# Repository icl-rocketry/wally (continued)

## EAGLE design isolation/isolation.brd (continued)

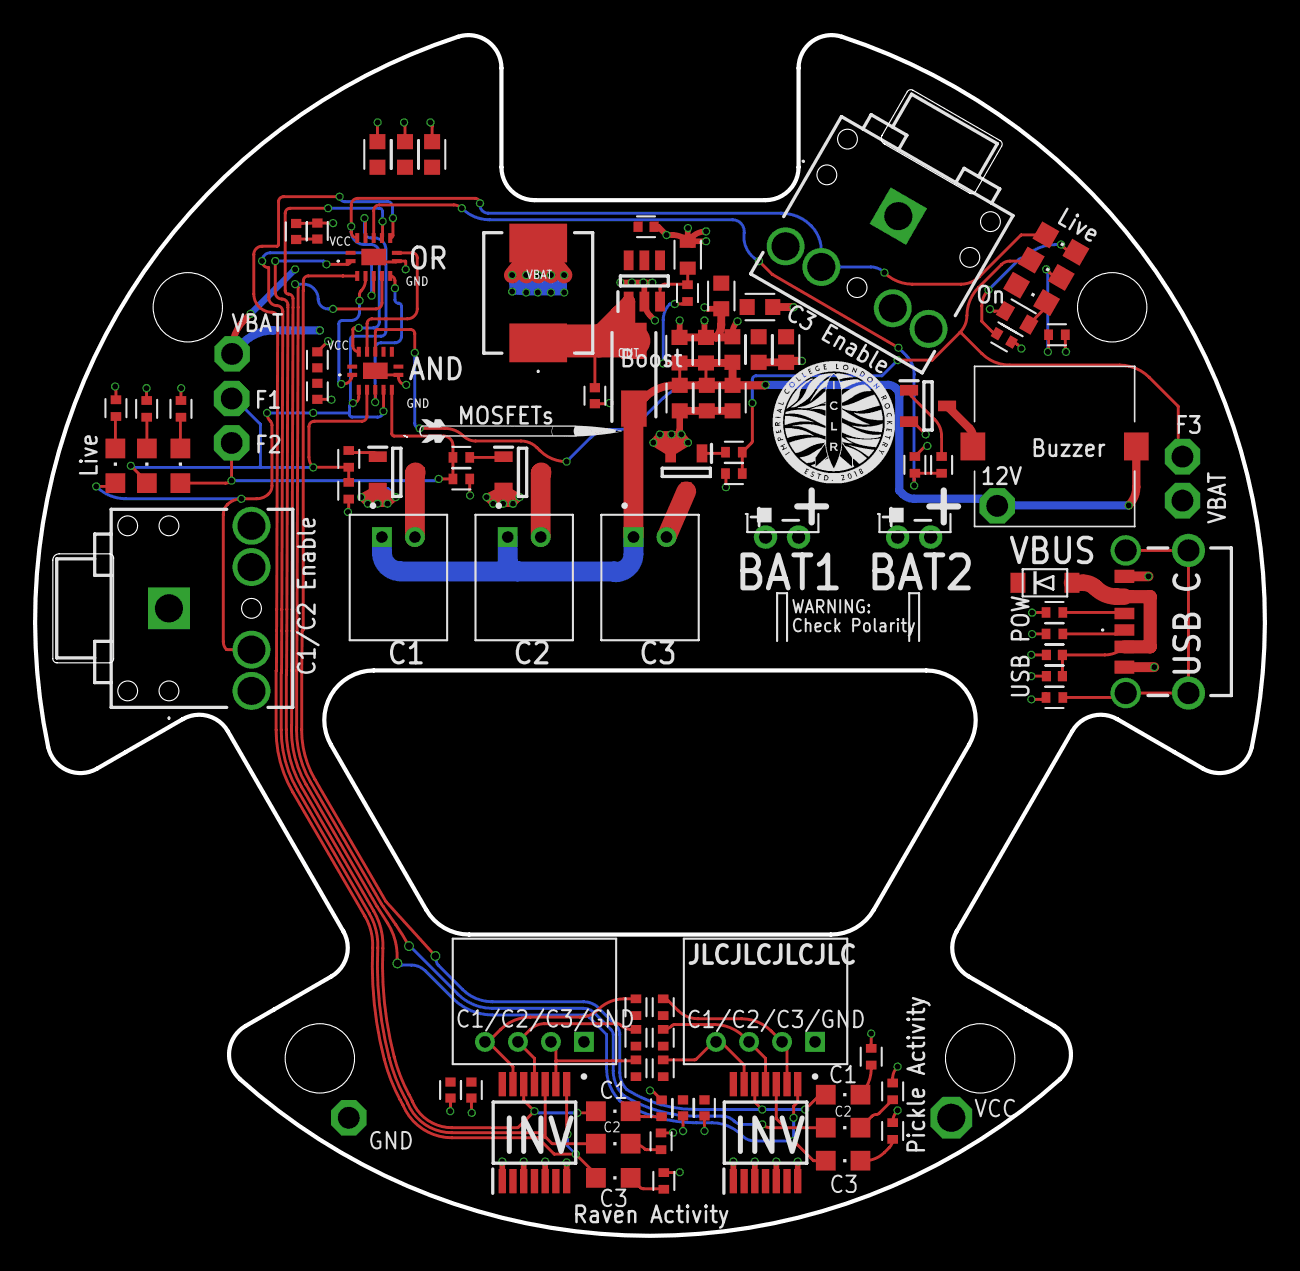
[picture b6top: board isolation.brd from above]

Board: 2 copper layers, 74.5 x 72.7 mm, 99 parts (0 on the bottom side), 50 nets.

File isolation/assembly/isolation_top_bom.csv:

Comment,Designator,Footprint,LCSC Part #
1M,R2 R13,RESC1608X60,C22935
1u,C3 C9 C11 C13 C15,CAPC1608X85,C15849
5k1,R12 R14,RESC1608X60,C23186
10u,C1 C2 C16 C17 C18 C19,CAPC1608X85,C19702
10uH,L1,L0603,C1035
22u,C4 C5 C6 C7 C20 C21 C22,CAPC1608X85,C59461
68k,R3 R8 R9 R10 R11,RESC1608X60,C23231
75,R1,RESC1608X60,C4275
100,R6 R7,RESC1608X60,C22775
100n,C8 C10 C12 C14,CAPC1608X85,C14663
120,R4 R5 R15 R16 R17 R18 R19 R20 R21 R22 R23,RESC1608X60,C22787
470,R24 R25 R26 R27,RESC1608X60,C23179
10164359-00011LF,J7,1016435900011LF,
CMI-9705-85-SMT-TR,LS1,CMI970585SMTTR,
FDN359BN,IC5 IC6 IC7 IC8,SOT95P251X112-3N,C5290365
LEDG,LED3 LED5,CHIPLED_0805,C2297
LEDR,LED6 LED7 LED8 LED9 LED10 LED11 LED12 LED13 LED14,CHIPLED_0805,C84256
LEDW,LED1,CHIPLED_0805,C34499
LEDY,LED2 LED4,CHIPLED_0805,C2296
SN74HC14PWR,IC2,SOP65P640X120-14N,SN74HC14PWR
SN74HCS08DYYR,IC4,SOP50P326X110-14N,
SN74HCS32BQAR,IC3,SN74HCS32BQAR,
SSA34-E3_5AT,D1,DIOM5127X229N,C22452
USBDiode,D2,SOD-123FL,C64898
XTLV61048DBVR,IC1,SOT95P280X145-6N,C2861467

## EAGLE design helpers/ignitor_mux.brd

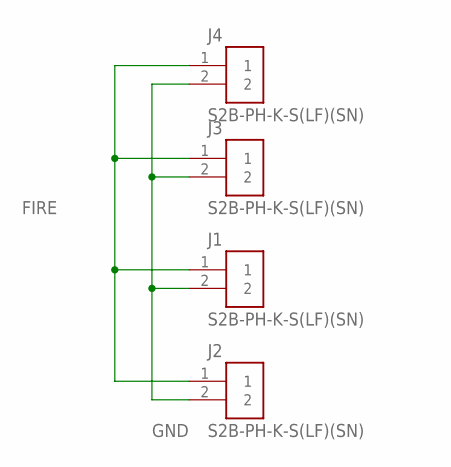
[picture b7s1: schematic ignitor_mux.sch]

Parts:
J1, J2, J3, J4: S2B-PH-K-S(LF)(SN)

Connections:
FIRE: J1.1, J2.1, J3.1, J4.1
GND: J1.2, J2.2, J3.2, J4.2

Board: 2 copper layers, 4 parts (0 on the bottom side), 2 nets, no tracks yet.

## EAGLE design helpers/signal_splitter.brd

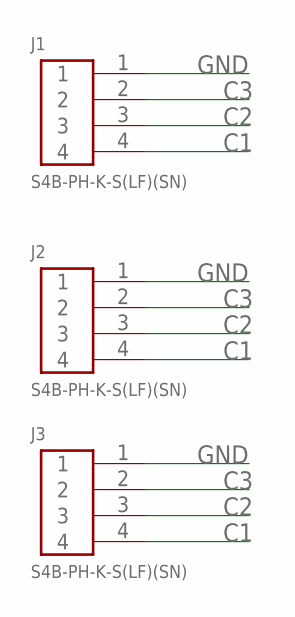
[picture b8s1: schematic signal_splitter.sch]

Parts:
J1, J2, J3: S4B-PH-K-S(LF)(SN)

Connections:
C1: J1.4, J2.4, J3.4
C2: J1.3, J2.3, J3.3
C3: J1.2, J2.2, J3.2
GND: J1.1, J2.1, J3.1

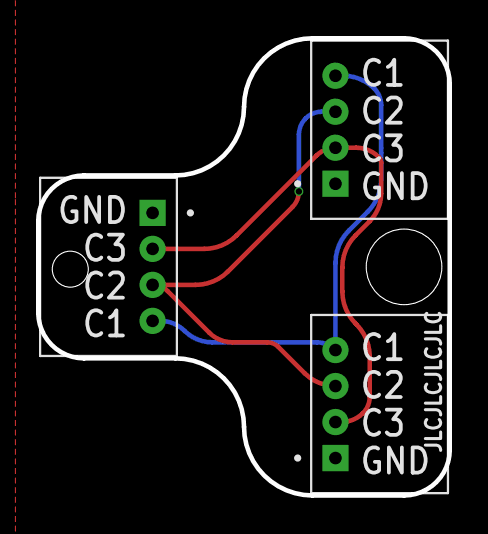
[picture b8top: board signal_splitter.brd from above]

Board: 2 copper layers, 22.9 x 25.4 mm, 3 parts (0 on the bottom side), 4 nets.

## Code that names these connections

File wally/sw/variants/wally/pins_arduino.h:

#ifndef Pins_Arduino_h
#define Pins_Arduino_h

#include <stdint.h>
#include "soc/soc_caps.h"

#define USB_VID            0x239A
#define USB_PID            0x8145
#define USB_MANUFACTURER   "ICLR"
#define USB_PRODUCT        "WALLY"
#define USB_SERIAL         ""   // Empty string for MAC adddress

#define PIN_BUTTON1     0  // BOOT0 switch

// UART
static const uint8_t TX0 = 43;
static const uint8_t RX0 = 44;

static const uint8_t TX1 = 17;
static const uint8_t RX1 = 18;

// I2C
static const uint8_t SDA0 = 47;
static const uint8_t SCL0 = 21;

static const uint8_t SDA1 = 5;
static const uint8_t SCL1 = 4;

// SD
static const uint8_t SD_CS   = 14;
static const uint8_t SD_DO   = 42;
static const uint8_t SD_CLK  = 39;
static const uint8_t SD_DI   = 21;

// Radio
static const uint8_t RAD_CS   = 39;
static const uint8_t RAD_DO   = 37;
static const uint8_t RAD_CLK  = 36;
static const uint8_t RAD_DI   = 38;
static const uint8_t RAD_RST  = 40;
static const uint8_t RAD_DIO1 = 42;
static const uint8_t RAD_DIO2 = 2;
static const uint8_t RAD_DIO3 = 1;
static const uint8_t RAD_RXEN  = 35;
static const uint8_t RAD_TXEN  = 41;
static const uint8_t RAD_BUSY = 48;

// SPI defaults (for compatibility with SPI lib)
static const uint8_t SCK  = RAD_CLK;
static const uint8_t MISO = RAD_DO;
static const uint8_t MOSI = RAD_DI;
static const uint8_t SS   = RAD_CS;

// I2C defaults (for compatibility with Wire lib)
static const uint8_t SDA = SDA0;
static const uint8_t SCL = SCL0;

// GPIO
static const uint8_t A0 = 8;
static const uint8_t A1 = 10;
static const uint8_t A2 = 9;
static const uint8_t A3 = 6;
static const uint8_t A4 = 16;

#define LED_R    8
#define LED_Y   10
#define LED_G    9

// VSENSE
static const uint8_t VSENSE = 7;

// PPS
static const uint8_t PPS = 15;

#endif /* Pins_Arduino_h */

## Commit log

2023-01-31 Wally
2023-01-31 Learning to use eagle
2023-02-07 wally board with gps and lora
2023-03-04 did code stuff
2023-03-07 sorry bout this
2023-03-07 tried to continue code
2023-03-21 complete code
2023-04-28 Added lora code (Doesn't work)
2023-05-20 Tiny GPS Uploaded
    Have installed tiny GPS module to Wally. (As advised by Shrey) :D
2023-05-20 Tiny GPS added
    I have added tiny gps as advised by Shrey to our lora branch. After having to use terminal wizzardry to add it (pain) :(
2023-05-20 Added Tiny GPS module
    As advised by Shrey
2023-05-23 LoRa Library Added
    Added the LoRa library as advised by Akshat.
2023-05-23 Create SX126x-Arduino
    LoRa library added as advised by Akshat:
    https://github.com/beegee-tokyo/SX126x-Arduino
2023-12-12 github testing 1.
    just testing on push/pulling
2023-12-12 deleted fixed
2023-12-12 creation of the file
2023-12-12 initial code
2023-12-12 Points in a plot for test rocket
2024-01-23 Update test data generation
    Creates time received values array for all ground stations for our full parabola fake rocket flight
2024-01-27 Update testdatagen.py
    Began working on the code to reconstruct the trajectory from the time recorded.
2024-01-30 some disaster
2024-02-03 03 Feb 2024
    Calculated point on intersection + coordinates of the point. Need to find normal vector to continue.
2024-02-06 final problem
2024-02-10 tests
2024-02-10 z diff fix
2024-02-20 Add files via upload
    Initial PCB design for ground station
2024-02-24 sustainer wiring diagram
2024-02-24 Added SIRIUS_sustainer.drawio
2024-02-24 power arch
2024-02-24 main boards
2024-02-24 complete IO
2024-02-24 wiring
2024-02-24 add qd
2024-02-24 antennae
2024-02-24 thermocouple
2024-03-19 Add files via upload
    Version 1 of Ground Station PCB
2024-04-25 create blank schematics for isolation board
2024-04-25 battery connectors
2024-04-25 power indicator LED
2024-04-26 12v boost schematic complete
2024-04-26 headphone jacks for user input
2024-04-26 fix footprint for caps
2024-04-26 headphone jack with inverter
2024-04-26 jst inputs from flight computers
2024-04-26 invert raven inputs
2024-04-26 complete firing logic
2024-04-26 fire control mosfet
2024-04-26 pull down resistors on mosfets
2024-04-26 danger buzzer
2024-04-26 usb c power
2024-04-26 indicator LEDs with manual testing
2024-04-26 ust jst for power
2024-04-26 layout with stringers and xc
2024-04-26 2 sector approach
2024-04-26 switch to JST-PH
2024-04-27 physically placed
2024-04-27 manual routing complete
2024-04-27 set board outline from dxf
2024-04-27 pads for ext power in
2024-04-27 ground and vcc pours
2024-04-27 wire lower connectors
2024-04-27 more routing
2024-04-27 10mil dim line
2024-04-27 move to smaller inverter
2024-04-27 smaller OR IC
2024-04-27 2 pin ignitor connectors
2024-04-27 add test pads
2024-04-27 placed shrunken components
2024-04-27 central cutout
2024-04-27 final routing
2024-04-27 fix to drc
2024-04-27 add iclr logo
2024-04-27 import cutout from fusion
2024-04-27 add some bulk caps
2024-04-27 add credits :)
2024-04-27 add graphics
2024-04-27 pass jlc drc
2024-04-27 export assembly files
2024-04-27 label LEDs
2024-04-27 fix assembly
2024-04-27 generate gerber
2024-04-27 more clearance around vias
2024-04-27 make a mux board for ignitors
2024-04-28 generate gerber for mux
2024-04-28 create a jst splitter pcb
2024-04-28 finalise for order
2024-04-28 fix drc issues
2024-04-28 initialise wally design
    based on ESP32-S3 and AI Thinker RA01-H
2024-04-28 usb c port
2024-04-28 SIM7600G (treat as pin header)
2024-04-28 Boost circuit for SIM
2024-04-28 battery inputs
2024-04-28 LDO for 3v3
2024-04-28 add ds3231 rtc
    treat as 5 pin header
2024-04-28 reset switch
2024-04-28 switch to smaller esp
2024-04-28 add sensors
2024-04-28 sd schematic
2024-04-28 sensor schematic done
2024-04-29 caps!!!
2024-04-29 complete placement of flight board components
2024-04-29 add ground station gps support
2024-04-29 manual route important traces
    before letting autorouter do it for me lol
2024-04-29 more test points for mystery pins
2024-04-29 high current traces
2024-04-29 apply jlc drc
2024-04-29 spider vsim
2024-04-29 remove autotrace attempt
2024-04-29 autoroute with thicker traces
2024-04-29 add some status LEDs
2024-04-29 fix all airwires
2024-04-29 fix to jlc drc
2024-04-29 complete routing
2024-04-29 cutout so board can be safely beheaded
2024-04-29 add wally graphic
2024-04-29 iclr logo
2024-04-29 add 3d models
2024-04-30 wally ready for manufacture
2024-04-30 create signal splitter board
    4 pin jst ph (2mm), compatible with isolation board
2024-04-30 move helper boards to their own section
2024-04-30 swap usb c connector
2024-04-30 swap usb c
2024-04-30 swap usb c (again)
    now using USB4105-GF-A-120, consistent with WALLY
2024-04-30 update bom
2024-05-02 increase keepout area near break line
2024-05-02 cleanup
2024-05-14 remove parallel vbus diodes
2024-05-14 move all components to top
2024-05-14 flip all components to top
2024-05-14 reset layout
2024-05-14 reset routing
2024-05-15 increase pour spacing to allow filing
2024-05-15 add mill slot for headphone jack
2024-05-15 move traces away from edge
2024-05-15 add mosfet gate drive resistors
2024-05-15 initialise pdu board
2024-05-15 import outline from fusion, add mounts
2024-05-15 3 bat inputs
2024-05-15 initial mosfet with RC
2024-05-15 parallel mosfets
2024-05-15 fillet corners
2024-05-15 fix hole position
2024-05-15 add usb c (optional)
2024-05-15 add output with decoupling cap
2024-05-15 fill length with conns
2024-05-15 swap connector
2024-05-15 fully populate board
2024-05-15 optimise layout
2024-05-15 add status leds
2024-05-15 add 3d packages
2024-05-16 add useful markings
2024-05-16 add sirius graphic
2024-05-16 upload sim breakout docs
2024-05-16 fix lte orientation
2024-05-16 remove beheading zone
2024-05-16 fix gps pin order
2024-05-16 fix bat polarity
2024-05-16 add boot/reset buttons
2024-05-17 reroute
2024-05-17 tent vias
2024-05-17 generate prod files
2024-05-17 add esp pinout doc
2024-05-17 festive vias
2024-05-17 improve power delivery
2024-05-17 final prod files
2024-05-17 prod files
2024-05-17 remove legacy platformio
2024-05-17 move connectors around for better mech integration
2024-05-17 graphics improvements
2024-05-17 rebuild prod files
2024-05-17 switch to power only usb
2024-05-17 cutout for 3.5mm connector
2024-05-17 helper boards prod files
2024-05-17 add test fire points
2024-05-18 souvenir edition of pdu
2024-05-18 initialise platformio
2024-05-18 fix wally init
2024-05-18 add flash freq
2024-05-18 adapt devkit json
2024-05-18 initialise custom board variant
    based on adafruit metro s3 (both using WROOM)
2024-05-18 initialise LEDs as battery meter
2024-05-18 init spi pins
2024-05-18 pinlist
    created a pinlist for the arduino code - called pinlist_wally in the docs folder of wally
2024-05-18 i2c and pps init
2024-05-18 remove adafruit warning
    they didn't make this :)
2024-05-18 add two generic inputs to wally
    had two gpio left lol
2024-05-18 better voltage thresholds
2024-05-19 Revert "Create pio_ci.yml"
    This reverts commit 45a8668e021e8dd683310d109ec628e33cd33dc8.
2024-05-19 move rtc to separate i2c bus
    allows all sensors to run at high speed
2024-05-19 remove thermocouple amp
    makes more sense to have it externally and connected through i2c
2024-05-19 use smaller components where available
2024-05-19 change to lsm6dsv imu
    +- 32g and integrated sensor fusion
2024-05-20 add high range accel
2024-05-20 add extended range baro
2024-05-20 rewire qwiic connectors
2024-05-20 swap mag IC
2024-05-20 add gpio connector
2024-05-20 swap hr baro with bme
2024-05-20 swap to dps368
    dps310 is nrnd
2024-05-20 change i2c pullup vals
    move to 5k1 from 10k
2024-05-20 route new i2c traces
2024-05-20 new pdu outline from fusion
2024-05-20 export new pdu
2024-05-20 export new wally
2024-05-21 upudate pin assignments form wally v1.1
2024-05-21 bugfix
2024-05-21 add mounting hole, ground plane under usb data
2024-05-21 actions fix
2024-05-22 set platformio working dir
2024-05-22 increase inductor size
2024-05-22 phat inductor
2024-05-23 add solder pad jumpers to gnd
2024-05-24 work on the IMU.
2024-05-24 add axes markers
2024-05-25 continued on wally-imu
2024-05-26 invert pickle signals
2024-05-26 remove safe indicator led
    much easier to wire
2024-05-26 smaller footprints
2024-05-26 pullups on signal lines
2024-05-26 fix silkscreen after moving components
2024-05-26 switch to smaller and gate
2024-05-27 new wally-board focussed main code
    worked on the main file with Wally being the board, rather than examples.
2024-05-27 change to single big fet
2024-05-28 improve routing
    swap gnd and supply planes and then reroute everything
2024-05-28 improve cable routing for gs config
2024-05-29 final prod versions
2024-05-29 aluminium single layer version
    souvenir only lol (but still technically functional!)
2024-06-01 work on the magnetometer
2024-06-01 basicstart
2024-06-11 design cable tester
2024-06-21 make switch boards
2024-06-22 base GSM functions
2024-06-22 Added compression routines
2024-06-23 initialise radio platformio with radiolib
2024-06-23 add pin assignments for radio module
2024-06-23 initial radio module code
2024-06-23 initialise spi comm bus for radio
2024-06-23 add default spi pin assignments
    needed for compatibility with SPI.h
2024-06-23 add wally variant build flag
2024-06-23 init function with distinct spi bus
2024-06-24 interrupt based transmit
2024-06-24 radio module docs
2024-06-25 add i2c defaults
2024-06-25 ds3231 working now
2024-06-26 Updated pins_arduino.h
2024-06-26 3d model for headphone jack
2024-06-26 baro code
2024-06-28 working now
2024-06-28 barometer working
2024-06-29 add default pins for spi and i2c
2024-07-04 i2c scan on boot
2024-07-04 bme680 using bosch lib
2024-07-04 init imu custom lib
2024-07-04 imu manufacturer driver
2024-07-05 init gps code
2024-07-05 struct to pack data
2024-07-05 gpsdata in loop
